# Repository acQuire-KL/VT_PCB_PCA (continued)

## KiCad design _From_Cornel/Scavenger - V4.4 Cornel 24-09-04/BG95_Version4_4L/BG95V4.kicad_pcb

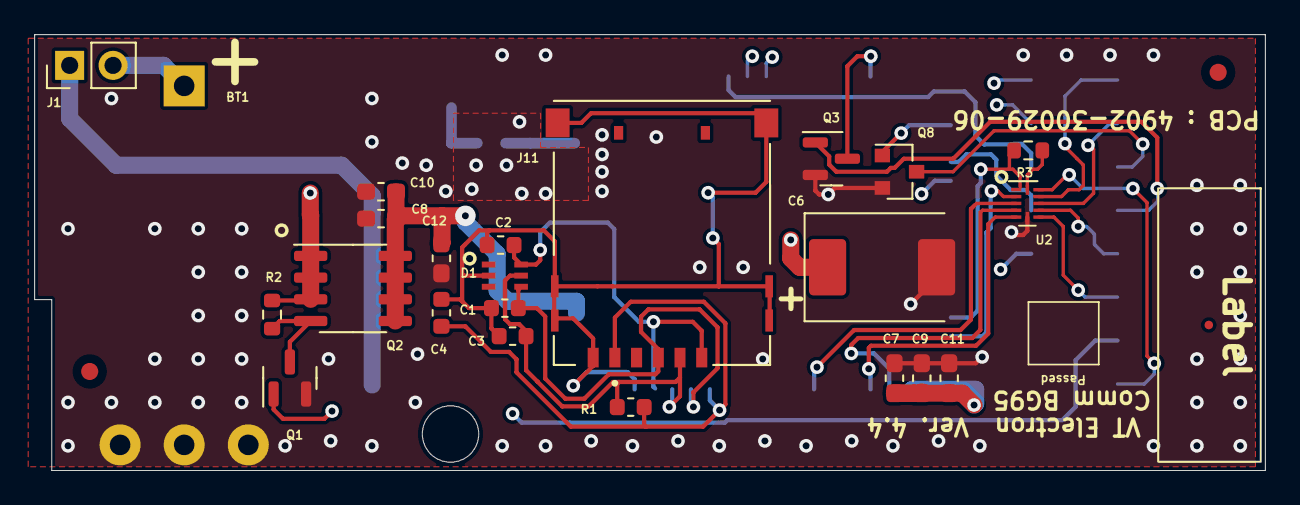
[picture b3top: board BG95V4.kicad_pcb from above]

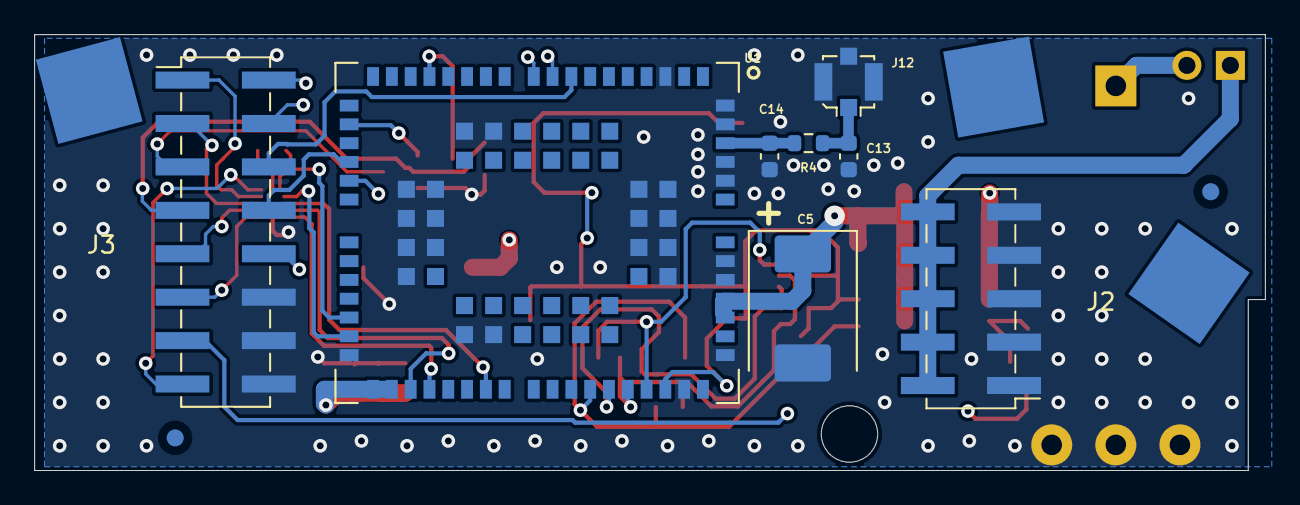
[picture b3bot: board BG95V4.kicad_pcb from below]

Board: 4 copper layers, 72.0 x 25.5 mm, 40 parts (13 on the bottom side), 33 nets.

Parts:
BT1: HLC1520-3P
C1, C2, C3: 33p; C_0603_1608Metric
C4: 100n; C_0603_1608Metric
C5, C6: TAJD477K006RNJ; CP_EIA-7361-38_AVX-V_Pad2.18x3.30mm_HandSolder
C7, C8: 100n; C_0603_1608Metric_Pad1.05x0.95mm_HandSolder
C9, C10: 33p; C_0603_1608Metric_Pad1.05x0.95mm_HandSolder
C11, C12: 10p; C_0603_1608Metric_Pad1.05x0.95mm_HandSolder
C13, C14: DNP; C_0603_1608Metric
D1: SMF05C.TCT; SC70-6
FID1, FID2, FID3, FID4: Fiducial; Fiducial_1mm_Mask2mm
H1: MountingHole; MountingHole_2.5mm Simpla
J1: DNP; PinHeader_1x02_P2.54mm_Vertical
J2: Conn_02x05_Counter_Clockwise; PinHeader_2x05_P2.54mm_Vertical_SMD_MOD
J3: Conn_02x08_Counter_Clockwise; PinHeader_2x08_P2.54mm_Vertical_SMD_MOD
J4, J5, J6: Conn_01x01_Male; TestPoint_Pad_5.1x5.1mm
J11: 78646-3001; MOLEX_78646-3001
J12: CONUFL001-SMD-T; U.FL_Molex_MCRF_73412-0110_Vertical
Q1, Q3, Q8: PDTC143XT; SOT-23
Q2: AO4459; SOIC-8_3.9x4.9mm_P1.27mm
R1: 15k; R_0603_1608Metric
R2, R3: 4k7; R_0603_1608Metric
R4: 0; R_0603_1608Metric
TP1: Eticheta
U1: BG95; XCVR_BG95M3LA-64-SGNS
U2: TXB0104RUT; Texas_R_PUQFN-N12

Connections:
/+3V3_UC: J3.8, U2.11 (VCCB)
/+3V6: J1.1, J2.6, J2.7, J2.8, J2.9, J2.10
/+3V6d: BT1.1 (+), J1.2, Q2.1 (S), Q2.2 (S), Q2.3 (S), R2.1
/Alim: J3.7, Q1.1 (B)
/D+: J3.10, U1.9 (USB_DP)
/D-: J3.9, U1.10 (USB_DM)
/DCD: U1.38 (DCD), U2.3 (A2)
/DTR: U1.30 (DTR), U2.2 (A1)
/PWRKEY: Q3.3 (C), U1.15 (PWRKEY)
/R: J3.12, U1.22 (DBG_RXD)
/RF_OUT: C14.1, R4.2, U1.60 (ANT_MAIN)
/RF_OUT1: C13.1, J12.1, R4.1
/RXD: U1.34 (RXD), U2.4 (A3)
/RxD: J3.6, U2.7 (B4)
/Status: Q8.1 (B), U1.20 (STATUS)
/T: J3.13, U1.23 (DBG_TXD)
/TXD: U1.35 (TXD), U2.5 (A4)
/TxD: J3.5, U2.8 (B3)
/VBAT: C5.1, C6.1, C7.1, C8.1, C9.1, C10.1, C11.1, C12.1, Q2.5 (D), Q2.6 (D), Q2.7 (D), Q2.8 (D), U1.32 (VBAT_BB), U1.33 (VBAT_BB), U1.52 (VBAT_RF), U1.53 (VBAT_RF)
/VDD_EXT: R3.1, U1.29 (VDD_EXT), U2.1 (VCCA)
/Vbus: J3.11, U1.8 (USB_VBUS)
/uCLK: C2.1, D1.6, J11.C3 (CLK), U1.46 (USIM_CLK)
/uDCD: J3.2, U2.9 (B2)
/uDTR: J3.1, U2.10 (B1)
/uData: C3.1, D1.5, J11.C7 (I/O), R1.2, U1.45 (USIM_DATA)
/uGND: C1.2, C2.2, C3.2, C4.1, D1.2, J11.C5 (GND), J11.G1 (GND), J11.G2 (GND), J11.G3 (GND), J11.G4 (GND), J11.G5 (GND), J11.G6 (GND), U1.47 (USIM_GND)
/uPWRKEY: J3.4, Q3.1 (B)
/uRST: C1.1, D1.4, J11.C2 (RST), U1.44 (USIM_RST)
/uStatus: J3.3, Q8.3 (C)
/uVDD: C4.2, J11.C1 (VCC), R1.1, U1.43 (USIM_VDD)
GND: BT1.2 (-), BT1.3 (-), BT1.4 (-), C5.2, C6.2, C7.2, C8.2, C9.2, C10.2, C11.2, C12.2, C13.2, C14.2, J2.1, J2.2, J2.3, J2.4, J2.5, J3.14, J3.15, J3.16, J12.2, Q1.2 (E), Q3.2 (E), Q8.2 (E), U1.3 (GND), U1.31 (GND), U1.48 (GND), U1.50 (GND), U1.54 (GND), U1.55 (GND), U1.58 (GND), U1.59 (GND), U1.61 (GND), U1.62 (GND), U1.67 (GND), U1.68 (GND), U1.69 (GND), U1.70 (GND), U1.71 (GND), U1.72 (GND), U1.73 (GND), U1.74 (GND), U1.79 (GND), U1.80 (GND), U1.81 (GND), U1.82 (GND), U1.89 (GND), U1.90 (GND), U1.91 (GND), U1.100 (GND), U1.101 (GND), U1.102 (GND), U2.6 (GND)
unnamed: Q1.3 (C), Q2.4 (G), R2.2
unnamed: R3.2, U2.12 (OE)

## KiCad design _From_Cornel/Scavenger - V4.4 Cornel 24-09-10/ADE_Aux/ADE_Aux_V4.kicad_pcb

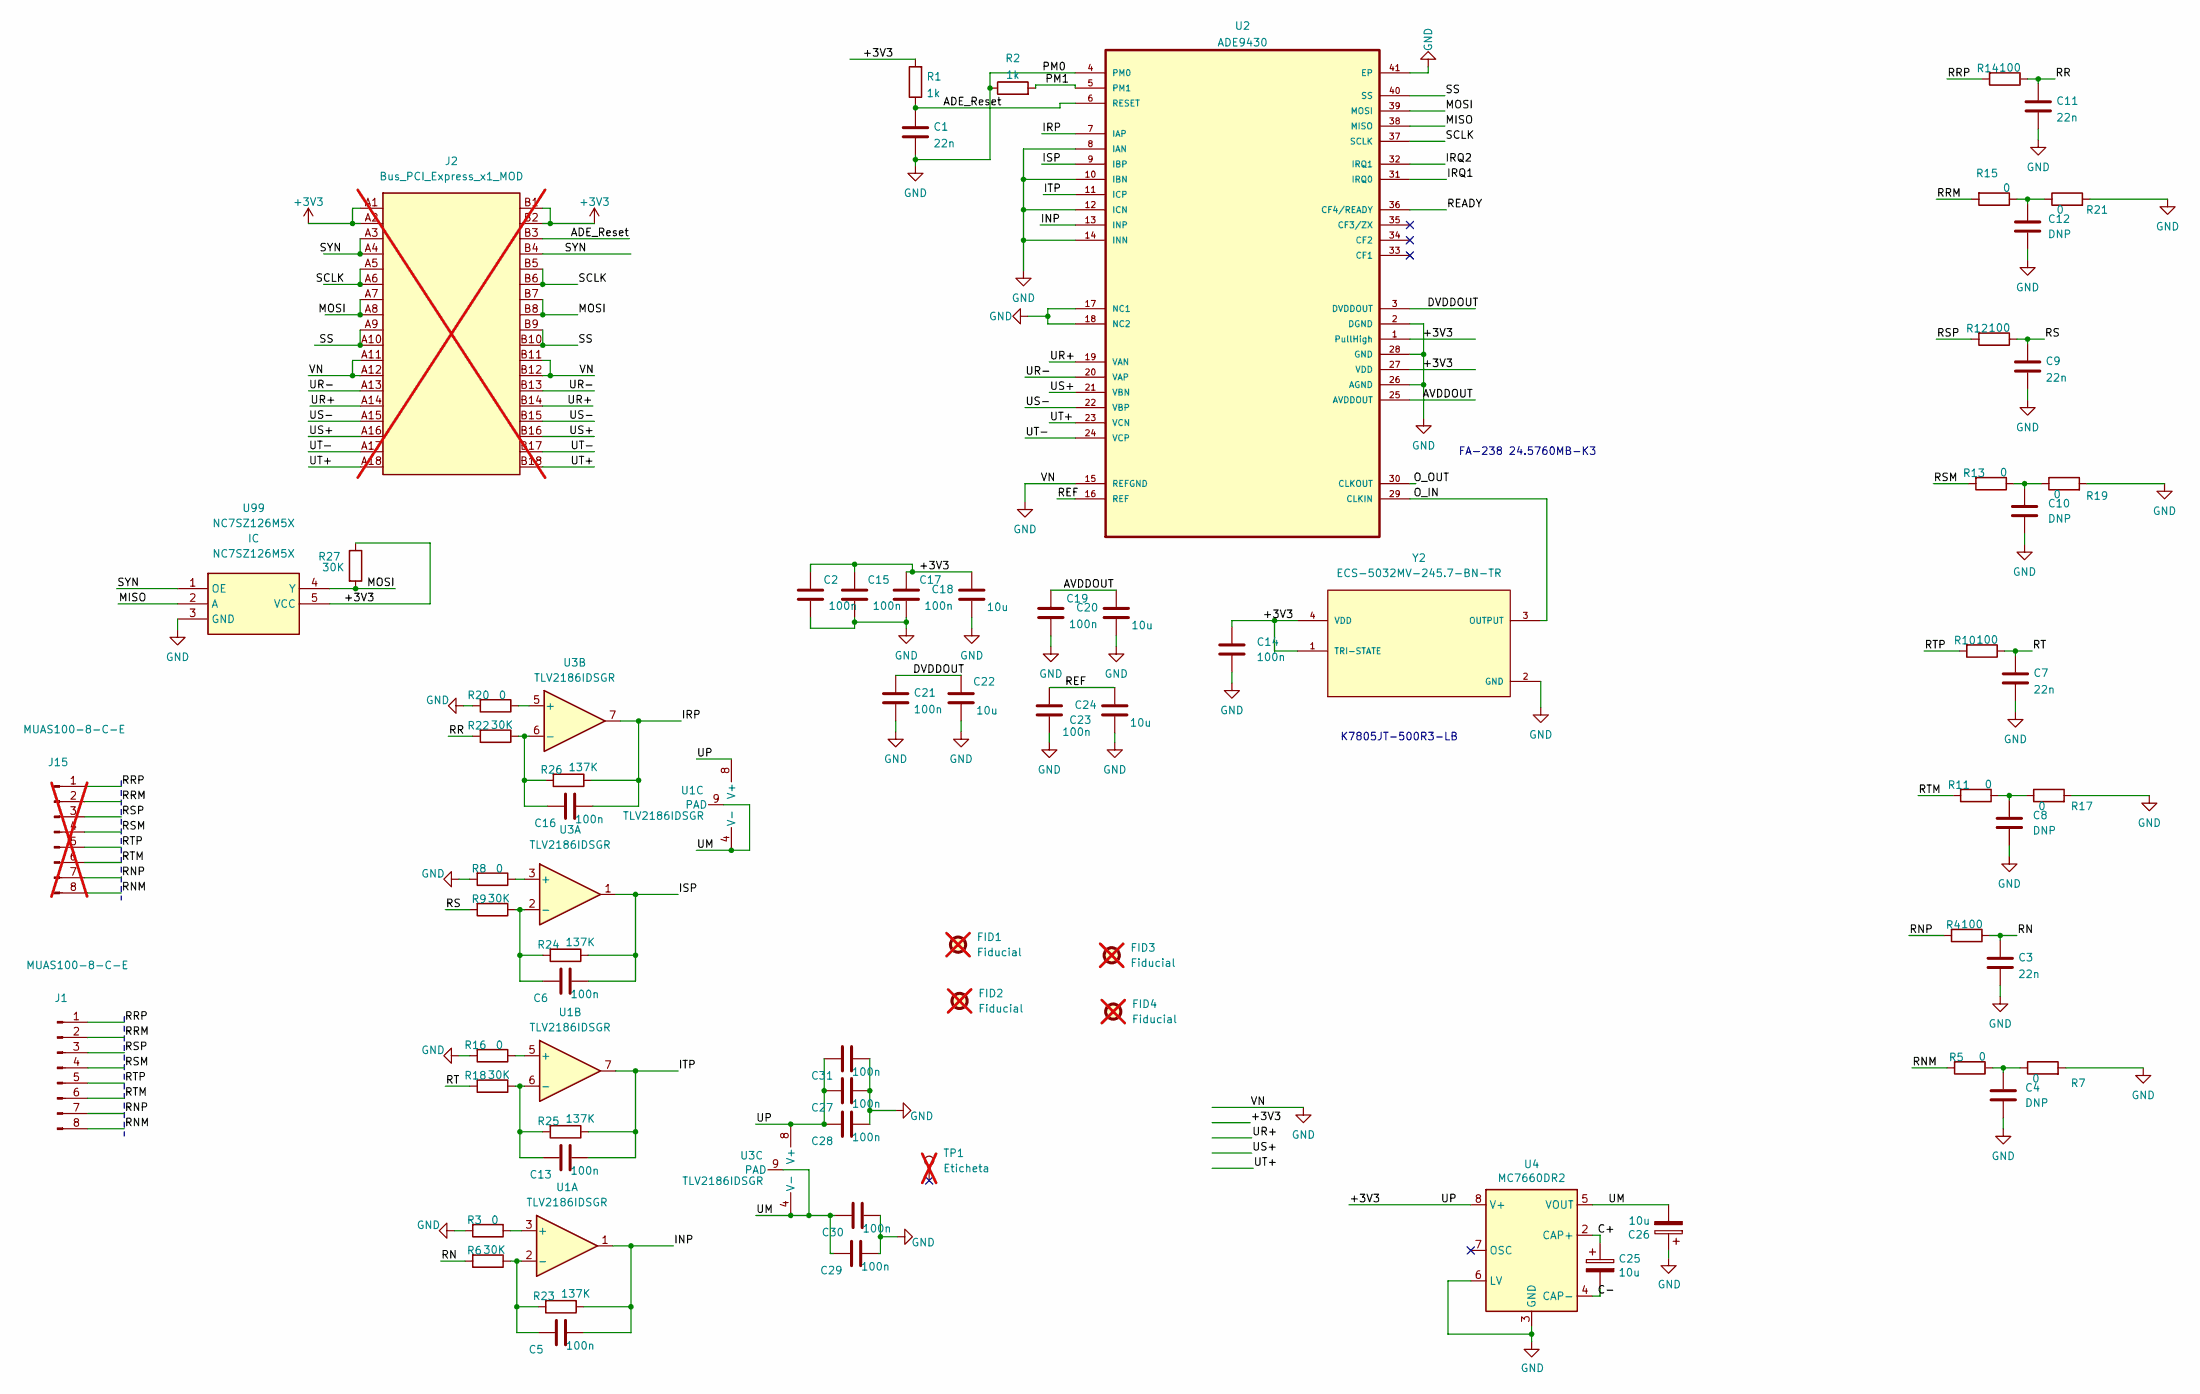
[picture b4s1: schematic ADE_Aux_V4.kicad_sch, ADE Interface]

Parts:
C1, C3, C7, C9, C11: 22n; C_0402_1005Metric
C2: 100n; C_0603_1608Metric
C4, C8, C10, C12: DNP; C_0402_1005Metric
C5, C6, C13, C14, C15, C16, C17, C19, C21, C23, C27, C28, C29, C30, C31: 100n; C_0402_1005Metric
C18, C20, C22, C24, C25, C26: 10u; C_1206_3216Metric
FID1, FID2, FID3, FID4: Fiducial; Fiducial_1mm_Mask2mm; not fitted
J1: MUAS100-8-C-E; A2501-SR08-XH8AWB
J2: Bus_PCI_Express_x1_MOD; BUS_PCIexpress_x1; not fitted
J15: MUAS100-8-C-E; PinHeader_1x08_P2.54mm_Vertical; not fitted
R1, R2: 1k; R_0402_1005Metric
R3, R5, R7, R8, R11, R13, R15, R16, R17, R19, R20, R21: 0; R_0402_1005Metric
R4, R10, R12, R14: 100; R_0402_1005Metric
R6, R9, R18, R22, R27: 30K; R_0402_1005Metric
R23, R24, R25, R26: 137K; R_0402_1005Metric
TP1: Eticheta; not fitted
U1, U3: TLV2186IDSGR; WSON-8-1EP_2x2mm_P0.5mm_EP0.9x1.6mm_ThermalVias
U2: ADE9430; MPN AD9115BCPZ
U4: MC7660DR2; SO-8_3.9x4.9mm_P1.27mm
U99: NC7SZ126M5X; Buffer3S; Manufacturer_Part_Number NC7SZ126M5X; Mouser Part Number 512-NC7SZ126M5X
Y2: ECS-5032MV-245.7-BN-TR; OSC_ECS-5032MV-245.7-BN-TR

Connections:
+3V3: C2.1, C14.1, C15.1, C17.1, C18.1, C27.2, C28.2, C31.2, J2.A1, J2.A2, J2.B1, J2.B2, R1.2, R27.1, U1.8 (V+), U2.1 (PullHigh), U2.27 (VDD), U3.8 (V+), U4.8 (V+), U99.5 (VCC), Y2.1 (TRI-STATE), Y2.4 (VDD)
/ADE_Reset: C1.1, J2.B3, R1.1, U2.6 (RESET)
/AVDDOUT: C19.1, C20.1, U2.25 (AVDDOUT)
/C+: C25.1, U4.2 (CAP+)
/C-: C25.2, U4.4 (CAP-)
/DVDDOUT: C21.1, C22.1, U2.3 (DVDDOUT)
/INP: C5.1, R23.1, U1.1, U2.13 (INP)
/IRP: C16.1, R26.1, U2.7 (IAP), U3.7
/IRQ1: U2.31 (IRQ0)
/IRQ2: U2.32 (IRQ1)
/ISP: C6.1, R24.1, U2.9 (IBP), U3.1
/ITP: C13.1, R25.1, U1.7, U2.11 (ICP)
/MISO: U2.38 (MISO), U99.2 (A)
/MOSI: J2.A7, J2.A8, J2.B7, J2.B8, R27.2, U2.39 (MOSI), U99.4 (Y)
/O_IN: U2.29 (CLKIN), Y2.3 (OUTPUT)
/O_OUT: U2.30 (CLKOUT)
/PM1: R2.2, U2.5 (PM1)
/READY: U2.36 (CF4/READY)
/REF: C23.1, C24.1, U2.16 (REF)
/RN: C3.1, R4.1, R6.2
/RNM: J1.8, J15.8, R5.2
/RNP: J1.7, J15.7, R4.2
/RR: C11.1, R14.1, R22.2
/RRM: J1.2, J15.2, R15.2
/RRP: J1.1, J15.1, R14.2
/RS: C9.1, R9.2, R12.1
/RSM: J1.4, J15.4, R13.2
/RSP: J1.3, J15.3, R12.2
/RT: C7.1, R10.1, R18.2
/RTM: J1.6, J15.6, R11.2
/RTP: J1.5, J15.5, R10.2
/SCLK: J2.A5, J2.A6, J2.B5, J2.B6, U2.37 (SCLK)
/SS: J2.A9, J2.A10, J2.B9, J2.B10, U2.40 (SS)
/SYN: J2.A3, J2.A4, J2.B4, U99.1 (OE)
/UM: C26.2, C29.2, C30.2, U1.4 (V-), U1.9 (PAD), U3.4 (V-), U3.9 (PAD), U4.5 (VOUT)
/UR+: J2.A14, J2.B14, U2.19 (VAN)
/UR-: J2.A13, J2.B13, U2.20 (VAP)
/US+: J2.A16, J2.B16, U2.21 (VBN)
/US-: J2.A15, J2.B15, U2.22 (VBP)
/UT+: J2.A18, J2.B18, U2.23 (VCN)
/UT-: J2.A17, J2.B17, U2.24 (VCP)
GND: C1.2, C2.2, C3.2, C4.2, C7.2, C8.2, C9.2, C10.2, C11.2, C12.2, C14.2, C15.2, C17.2, C18.2, C19.2, C20.2, C21.2, C22.2, C23.2, C24.2, C26.1, C27.1, C28.1, C29.1, C30.1, C31.1, J2.A11, J2.A12, J2.B11, J2.B12, R2.1, R3.2, R7.2, R8.2, R16.2, R17.2, R19.2, R20.2, R21.2, U2.2 (DGND), U2.4 (PM0), U2.8 (IAN), U2.10 (IBN), U2.12 (ICN), U2.14 (INN), U2.15 (REFGND), U2.17 (NC1), U2.18 (NC2), U2.26 (AGND), U2.28 (GND), U2.41 (EP), U4.3 (GND), U4.6 (LV), U99.3 (GND), Y2.2 (GND)
unnamed: C4.1, R5.1, R7.1
unnamed: C5.2, R6.1, R23.2, U1.2 (-)
unnamed: C6.2, R9.1, R24.2, U3.2 (-)
unnamed: C8.1, R11.1, R17.1
unnamed: C10.1, R13.1, R19.1
unnamed: C12.1, R15.1, R21.1
unnamed: C13.2, R18.1, R25.2, U1.6 (-)
unnamed: C16.2, R22.1, R26.2, U3.6 (-)
unnamed: R3.1, U1.3 (+)
unnamed: R8.1, U3.3 (+)
unnamed: R16.1, U1.5 (+)
unnamed: R20.1, U3.5 (+)

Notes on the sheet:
FA-238 24.5760MB-K3
K7805JT-500R3-LB

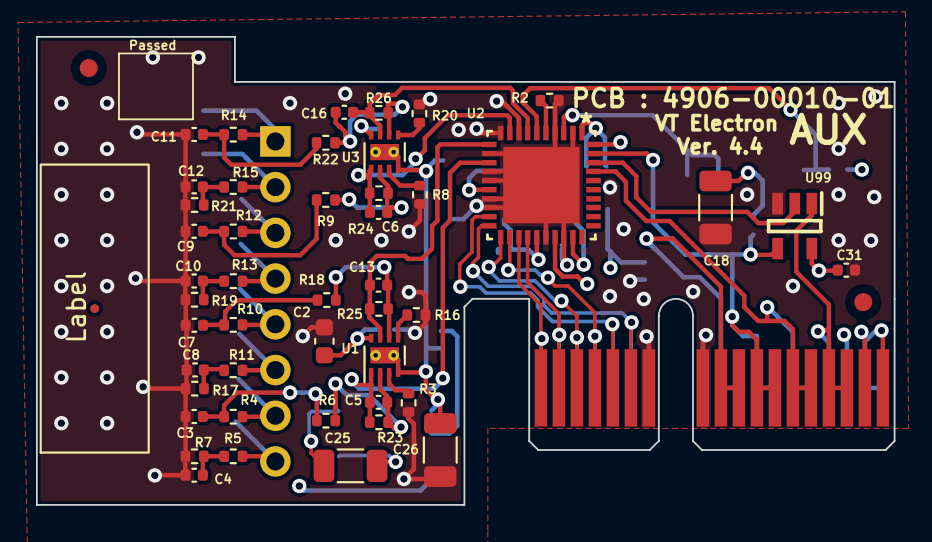
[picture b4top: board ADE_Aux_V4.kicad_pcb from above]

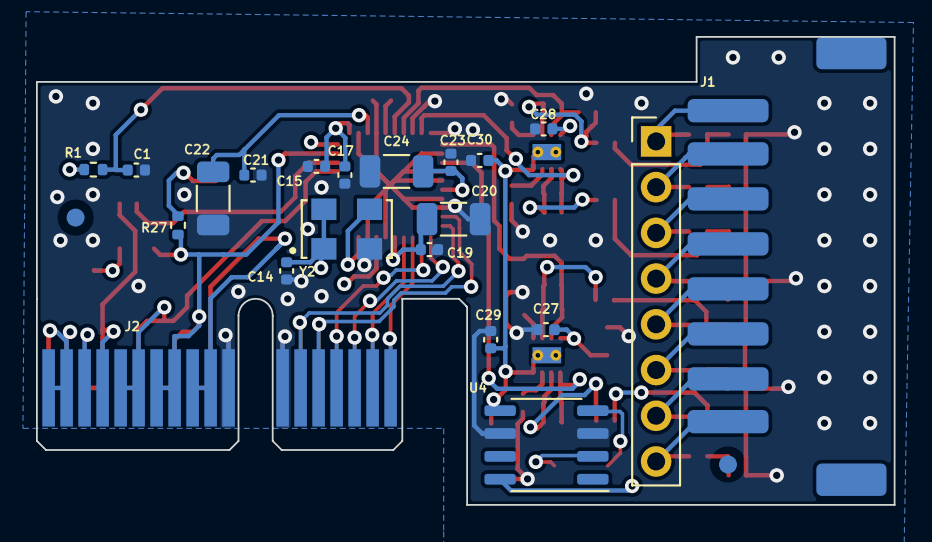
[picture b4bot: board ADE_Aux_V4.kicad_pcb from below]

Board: 4 copper layers, 47.6 x 26.0 mm, 72 parts (23 on the bottom side), 50 nets.

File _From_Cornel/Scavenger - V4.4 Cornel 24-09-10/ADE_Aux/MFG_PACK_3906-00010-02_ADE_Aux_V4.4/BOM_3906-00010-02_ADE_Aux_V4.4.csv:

"Id";"Designator";"Footprint";"Quantity";"Designation";"Supplier and ref";
1;"R25,R26,R24,R23";"R_0402_1005Metric";4;"137K";;;
2;"R18,R9,R6,R22,R27";"R_0402_1005Metric";5;"30K";;;
3;"R5,R20,R8,R11,R15,R21,R17,R7,R16,R3,R19,R13";"R_0402_1005Metric";12;"0";;;
4;"C11,C3,C7,C9,C1";"C_0402_1005Metric";5;"22n";;;
5;"C13,C16,C6,C5,C31,C28,C30,C23,C15,C27,C17,C14,C29,C19,C21";"C_0402_1005Metric";15;"100n";;;
6;"FID1,FID4,FID3,FID2";"Fiducial_1mm_Mask2mm";4;"Fiducial";;;
7;"C26,C18,C25,C20,C22,C24";"C_1206_3216Metric";6;"10u";;;
8;"C2";"C_0603_1608Metric";1;"100n";;;
9;"C4,C12,C10,C8";"C_0402_1005Metric";4;"DNP";;;
10;"TP1";"Eticheta";1;"Eticheta";;;
11;"R4,R14,R10,R12";"R_0402_1005Metric";4;"100";;;
12;"U3,U1";"WSON-8-1EP_2x2mm_P0.5mm_EP0.9x1.6mm_ThermalVias";2;"TLV2186IDSGR";;;
13;"U2";"ADE9430";1;"ADE9430";;;
14;"R2,R1";"R_0402_1005Metric";2;"1k";;;
15;"U99";"Buffer3S";1;"NC7SZ126M5X";;;
16;"Y2";"OSC_ECS-5032MV-245.7-BN-TR";1;"ECS-5032MV-245.7-BN-TR";;;
17;"J1";"A2501-SR08-XH8AWB";1;"MUAS100-8-C-E";;;
18;"J15";"PinHeader_1x08_P2.54mm_Vertical";1;"MUAS100-8-C-E";;;
19;"J2";"BUS_PCIexpress_x1";1;"Bus_PCI_Express_x1_MOD";;;
20;"U4";"SO-8_3.9x4.9mm_P1.27mm";1;"MC7660DR2";;;
